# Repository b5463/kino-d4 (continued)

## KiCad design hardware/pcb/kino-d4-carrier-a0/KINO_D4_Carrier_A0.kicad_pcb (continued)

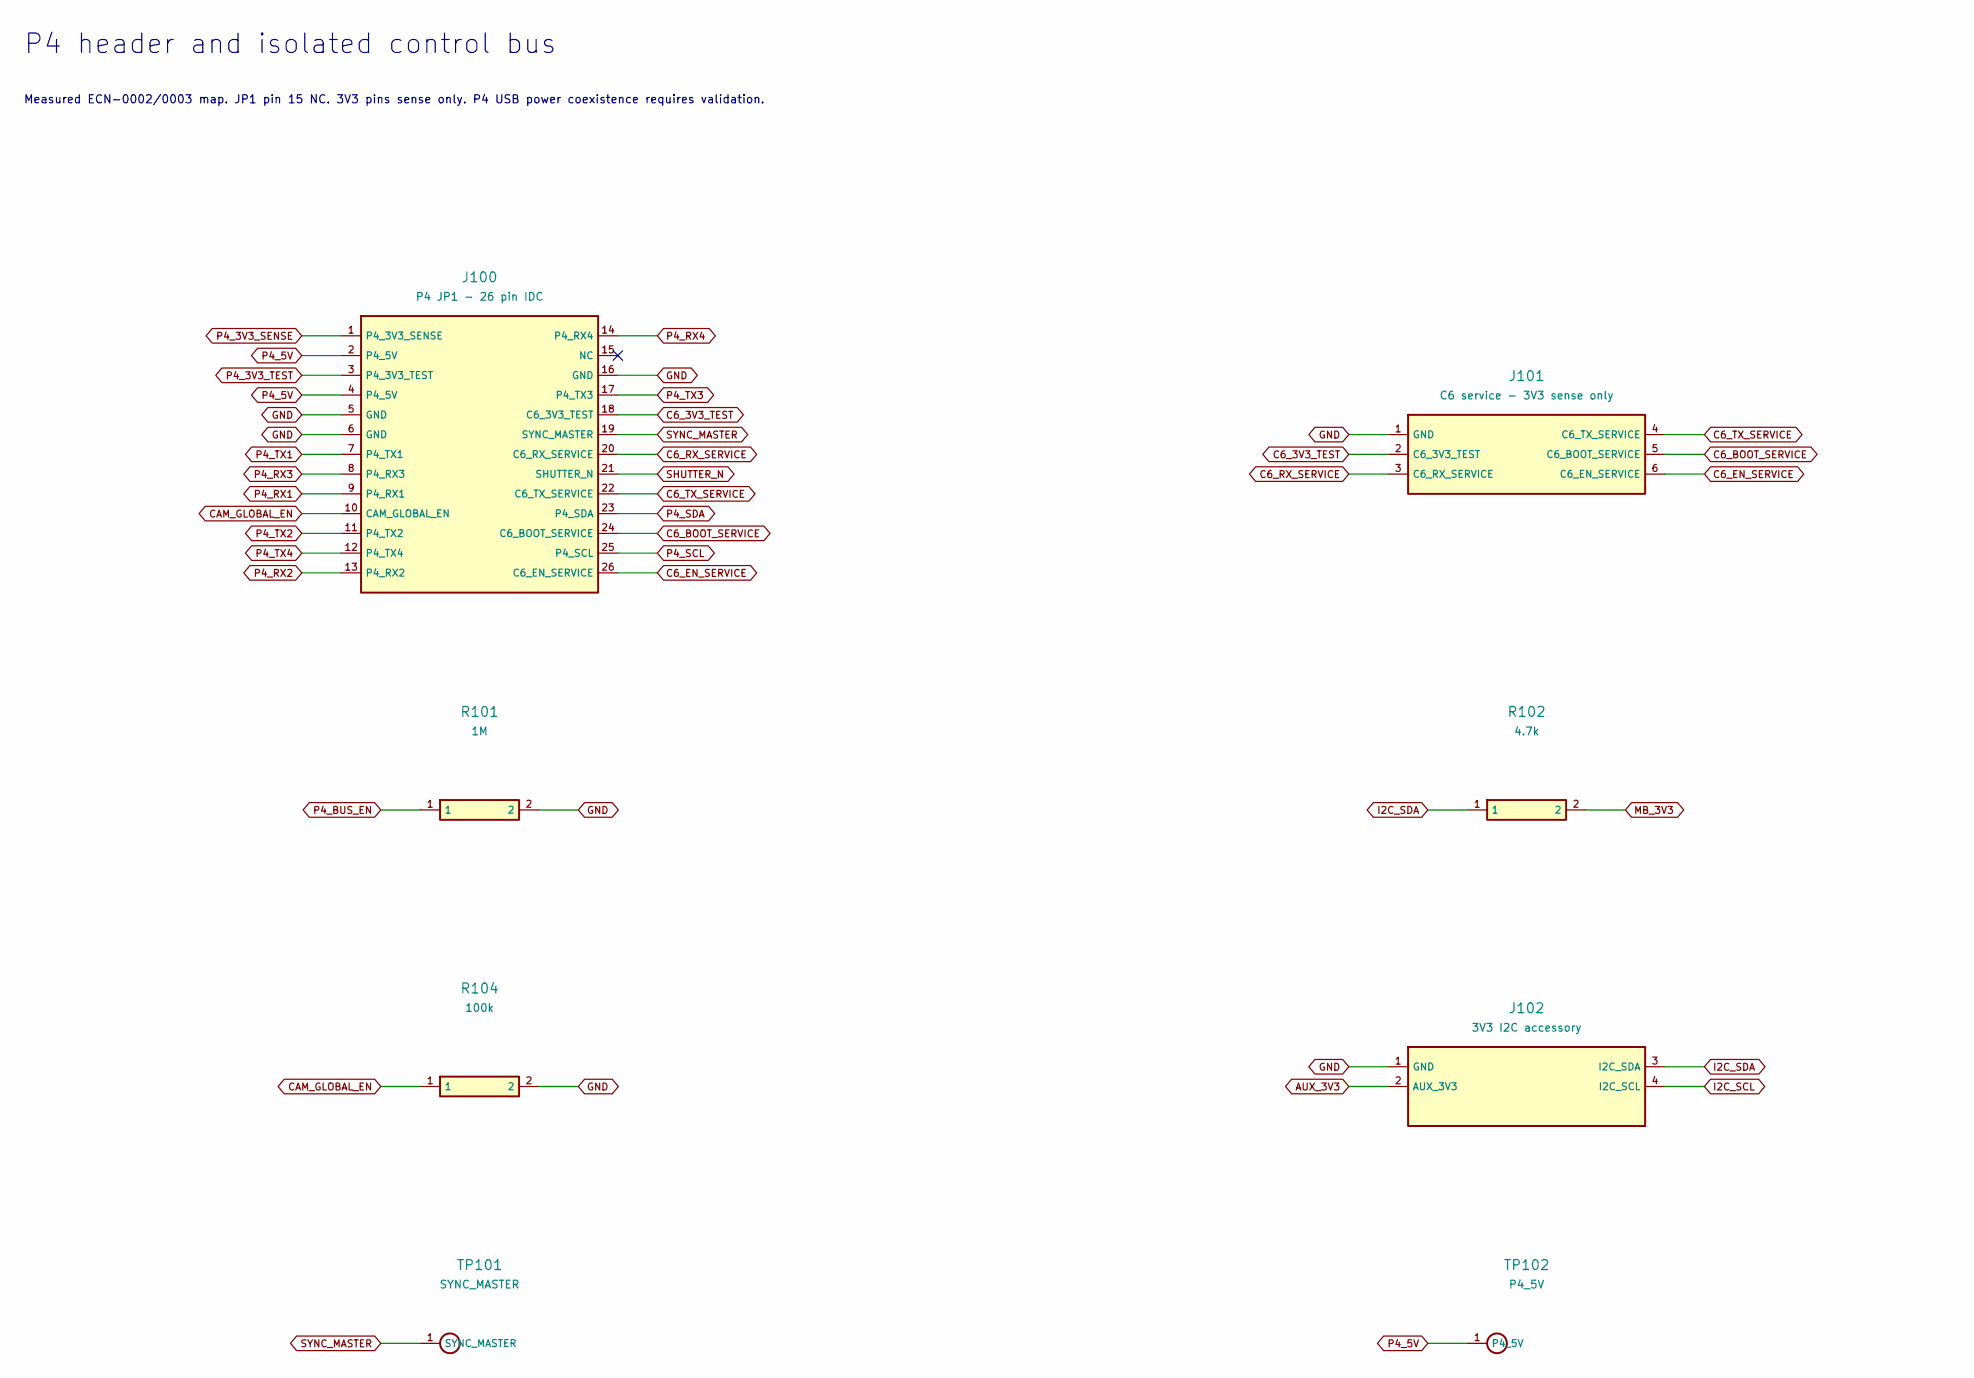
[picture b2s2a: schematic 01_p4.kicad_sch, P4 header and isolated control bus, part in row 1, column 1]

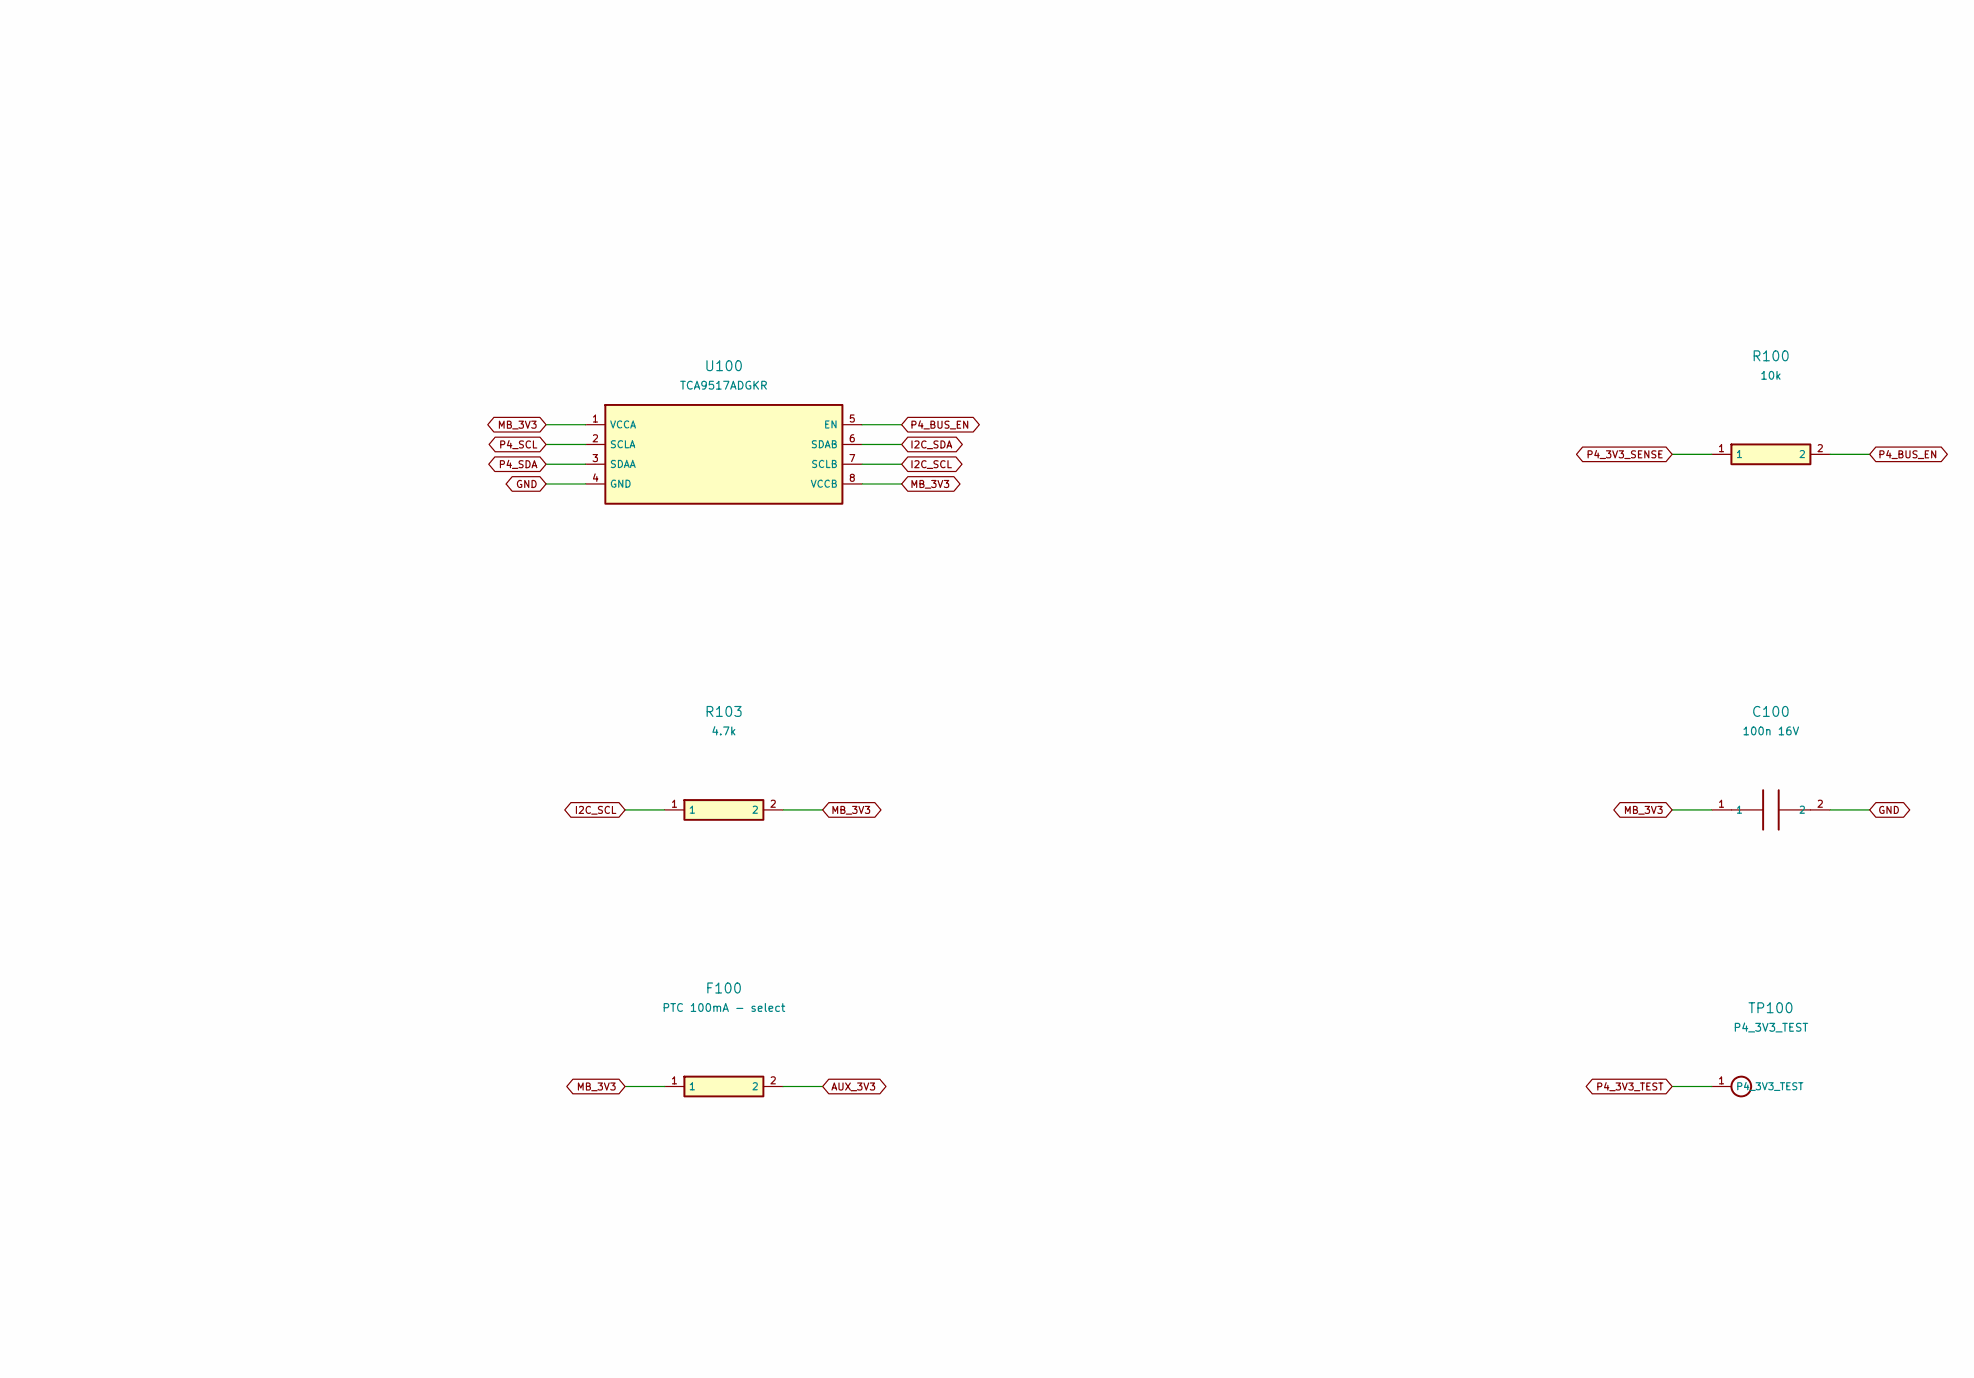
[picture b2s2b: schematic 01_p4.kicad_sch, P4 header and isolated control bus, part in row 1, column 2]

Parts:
C100: 100n 16V; C_0603_1608Metric
F100: PTC 100mA - select; Fuse_1206_3216Metric
J100: P4 JP1 - 26 pin IDC; IDC-Header_2x13_P2.54mm_Vertical
J101: C6 service - 3V3 sense only; PinHeader_1x06_P2.54mm_Vertical
J102: 3V3 I2C accessory; JST_GH_BM04B-GHS-TBT_1x04-1MP_P1.25mm_Vertical
R100: 10k; R_0603_1608Metric
R101: 1M; R_0603_1608Metric
R102, R103: 4.7k; R_0603_1608Metric
R104: 100k; R_0603_1608Metric
TP100: P4_3V3_TEST; TestPoint_Pad_D1.5mm
TP101: SYNC_MASTER; TestPoint_Pad_D1.5mm
TP102: P4_5V; TestPoint_Pad_D1.5mm
U100: TCA9517ADGKR; VSSOP-8_3x3mm_P0.65mm

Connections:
AUX_3V3: F100.2, J102.2 (AUX_3V3)
C6_3V3_TEST: J100.18 (C6_3V3_TEST), J101.2 (C6_3V3_TEST)
C6_BOOT_SERVICE: J100.24 (C6_BOOT_SERVICE), J101.5 (C6_BOOT_SERVICE)
C6_EN_SERVICE: J100.26 (C6_EN_SERVICE), J101.6 (C6_EN_SERVICE)
C6_RX_SERVICE: J100.20 (C6_RX_SERVICE), J101.3 (C6_RX_SERVICE)
C6_TX_SERVICE: J100.22 (C6_TX_SERVICE), J101.4 (C6_TX_SERVICE)
CAM_GLOBAL_EN: J100.10 (CAM_GLOBAL_EN), R104.1; also elsewhere on the board
I2C_SCL: J102.4 (I2C_SCL), R103.1, U100.7 (SCLB); also elsewhere on the board
I2C_SDA: J102.3 (I2C_SDA), R102.1, U100.6 (SDAB); also elsewhere on the board
MB_3V3: C100.1, F100.1, R102.2, R103.2, U100.1 (VCCA), U100.8 (VCCB); also elsewhere on the board
P4_3V3_SENSE: J100.1 (P4_3V3_SENSE), R100.1
P4_3V3_TEST: J100.3 (P4_3V3_TEST), TP100.1
P4_5V: J100.2 (P4_5V), J100.4 (P4_5V), TP102.1; also elsewhere on the board
P4_BUS_EN: R100.2, R101.1, U100.5 (EN); also elsewhere on the board
P4_RX1: J100.9 (P4_RX1); also elsewhere on the board
P4_RX2: J100.13 (P4_RX2); also elsewhere on the board
P4_RX3: J100.8 (P4_RX3); also elsewhere on the board
P4_RX4: J100.14 (P4_RX4); also elsewhere on the board
P4_SCL: J100.25 (P4_SCL), U100.2 (SCLA)
P4_SDA: J100.23 (P4_SDA), U100.3 (SDAA)
P4_TX1: J100.7 (P4_TX1); also elsewhere on the board
P4_TX2: J100.11 (P4_TX2); also elsewhere on the board
P4_TX3: J100.17 (P4_TX3); also elsewhere on the board
P4_TX4: J100.12 (P4_TX4); also elsewhere on the board
SHUTTER_N: J100.21 (SHUTTER_N); also elsewhere on the board
SYNC_MASTER: J100.19 (SYNC_MASTER), TP101.1; also elsewhere on the board

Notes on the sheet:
P4 header and isolated control bus
Measured ECN-0002/0003 map. JP1 pin 15 NC. 3V3 pins sense only. P4 USB power coexistence requires validation.

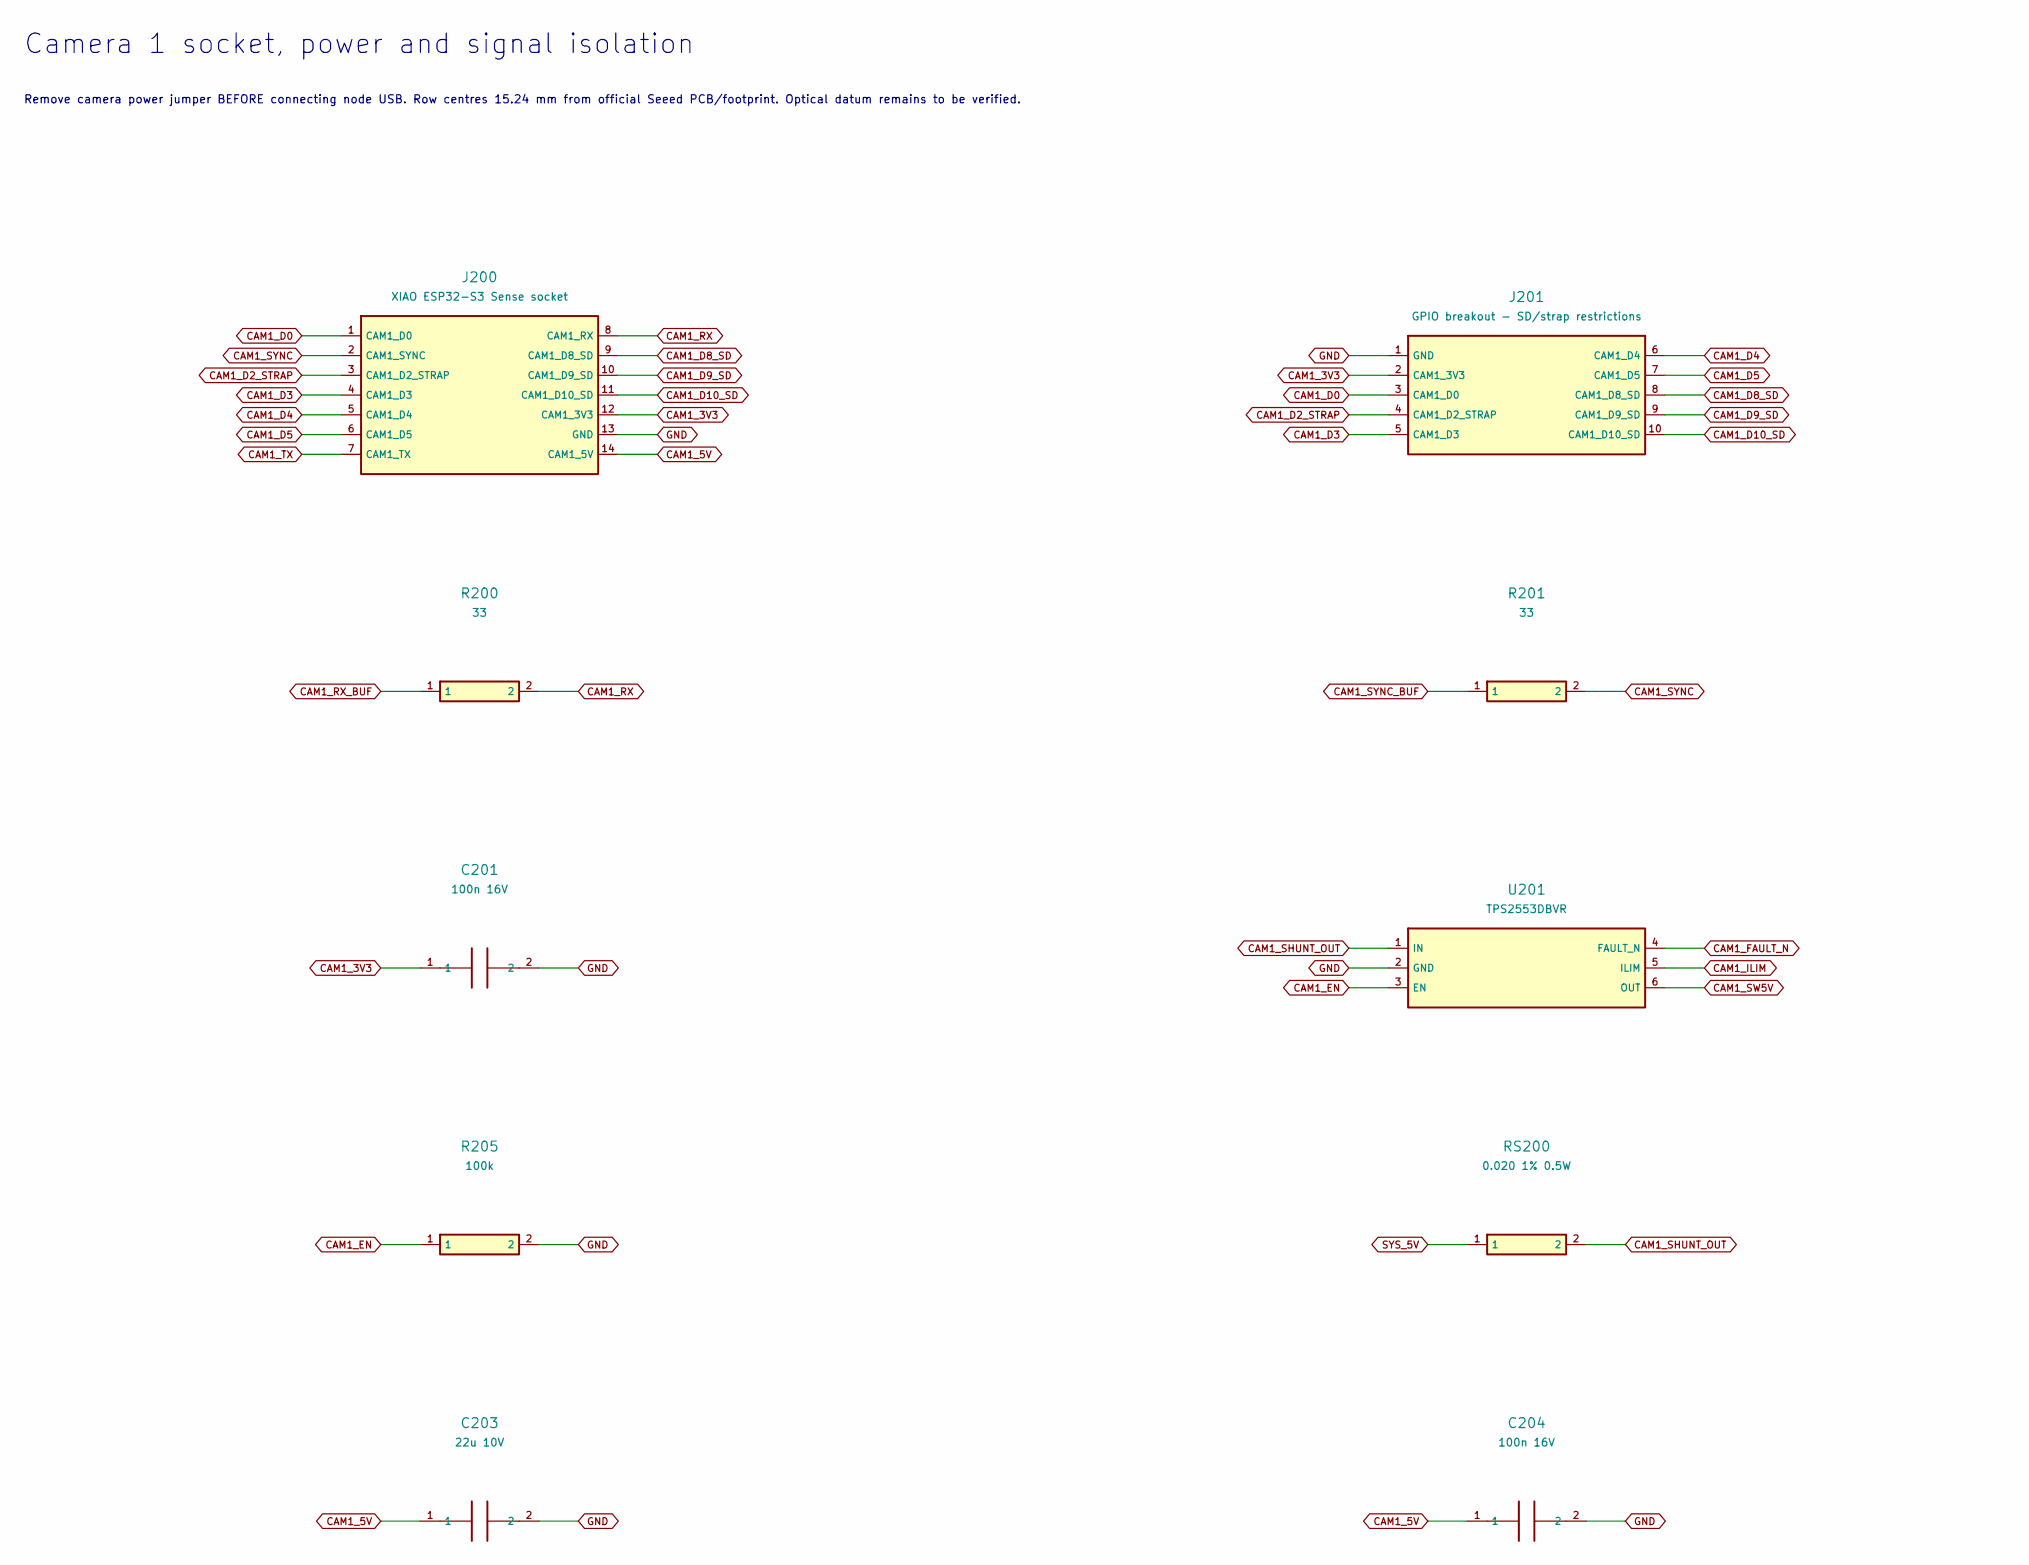
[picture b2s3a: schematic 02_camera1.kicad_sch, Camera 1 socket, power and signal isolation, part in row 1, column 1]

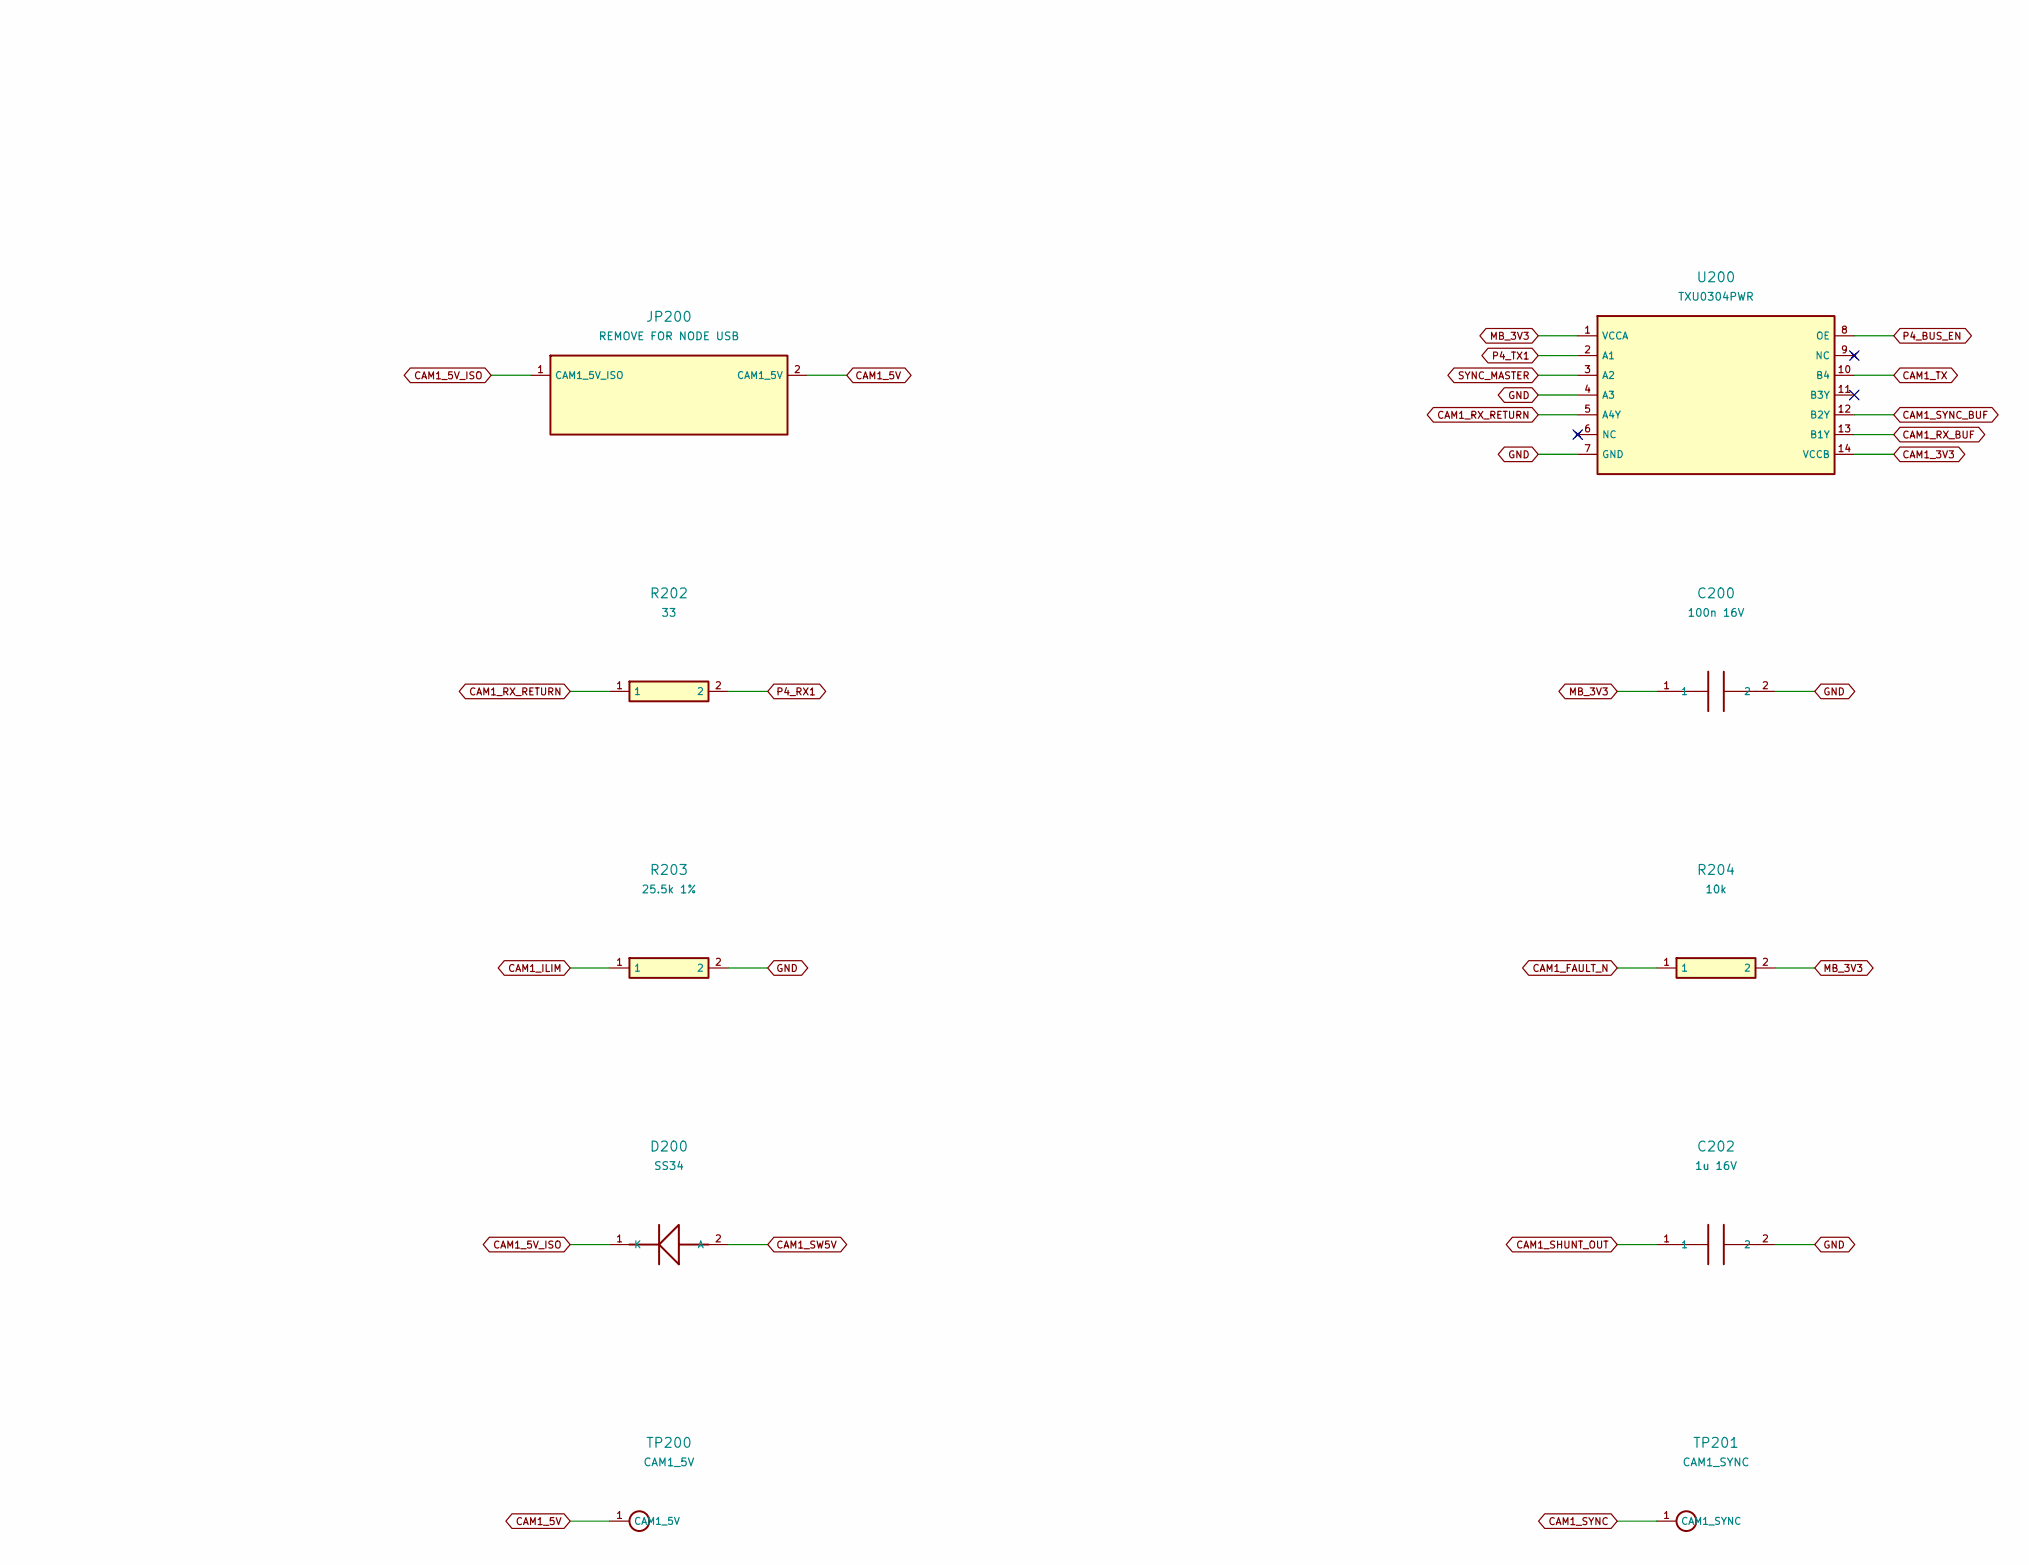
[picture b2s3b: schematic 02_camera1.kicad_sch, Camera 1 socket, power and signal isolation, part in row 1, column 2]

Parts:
C200, C201, C204: 100n 16V; C_0603_1608Metric
C202: 1u 16V; C_0603_1608Metric
C203: 22u 10V; C_0805_2012Metric
D200: SS34; D_SMA
J200: XIAO ESP32-S3 Sense socket; XIAO_Socket_15.24mm
J201: GPIO breakout - SD/strap restrictions; PinHeader_2x05_P2.54mm_Vertical
JP200: REMOVE FOR NODE USB; PinHeader_1x02_P2.54mm_Vertical
R200, R201, R202: 33; R_0603_1608Metric
R203: 25.5k 1%; R_0603_1608Metric
R204: 10k; R_0603_1608Metric
R205: 100k; R_0603_1608Metric
RS200: 0.020 1% 0.5W; R_1206_3216Metric
TP200: CAM1_5V; TestPoint_Pad_D1.5mm
TP201: CAM1_SYNC; TestPoint_Pad_D1.5mm
U200: TXU0304PWR; TSSOP-14_4.4x5mm_P0.65mm
U201: TPS2553DBVR; SOT-23-6

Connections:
CAM1_3V3: C201.1, J200.12 (CAM1_3V3), J201.2 (CAM1_3V3), U200.14 (VCCB)
CAM1_5V: C203.1, C204.1, J200.14 (CAM1_5V), JP200.2 (CAM1_5V), TP200.1
CAM1_5V_ISO: D200.1 (K), JP200.1 (CAM1_5V_ISO)
CAM1_D0: J200.1 (CAM1_D0), J201.3 (CAM1_D0)
CAM1_D2_STRAP: J200.3 (CAM1_D2_STRAP), J201.4 (CAM1_D2_STRAP)
CAM1_D3: J200.4 (CAM1_D3), J201.5 (CAM1_D3)
CAM1_D4: J200.5 (CAM1_D4), J201.6 (CAM1_D4)
CAM1_D5: J200.6 (CAM1_D5), J201.7 (CAM1_D5)
CAM1_D8_SD: J200.9 (CAM1_D8_SD), J201.8 (CAM1_D8_SD)
CAM1_D9_SD: J200.10 (CAM1_D9_SD), J201.9 (CAM1_D9_SD)
CAM1_D10_SD: J200.11 (CAM1_D10_SD), J201.10 (CAM1_D10_SD)
CAM1_EN: R205.1, U201.3 (EN); also elsewhere on the board
CAM1_FAULT_N: R204.1, U201.4 (FAULT_N); also elsewhere on the board
CAM1_ILIM: R203.1, U201.5 (ILIM)
CAM1_RX: J200.8 (CAM1_RX), R200.2
CAM1_RX_BUF: R200.1, U200.13 (B1Y)
CAM1_RX_RETURN: R202.1, U200.5 (A4Y)
CAM1_SHUNT_OUT: C202.1, RS200.2, U201.1 (IN); also elsewhere on the board
CAM1_SW5V: D200.2 (A), U201.6 (OUT)
CAM1_SYNC: J200.2 (CAM1_SYNC), R201.2, TP201.1
CAM1_SYNC_BUF: R201.1, U200.12 (B2Y)
CAM1_TX: J200.7 (CAM1_TX), U200.10 (B4)
MB_3V3: C200.1, R204.2, U200.1 (VCCA); also elsewhere on the board
P4_BUS_EN: U200.8 (OE); also elsewhere on the board
P4_RX1: R202.2; also elsewhere on the board
P4_TX1: U200.2 (A1); also elsewhere on the board
SYNC_MASTER: U200.3 (A2); also elsewhere on the board
SYS_5V: RS200.1; also elsewhere on the board

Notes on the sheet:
Camera 1 socket, power and signal isolation
Remove camera power jumper BEFORE connecting node USB. Row centres 15.24 mm from official Seeed PCB/footprint. Optical datum remains to be verified.

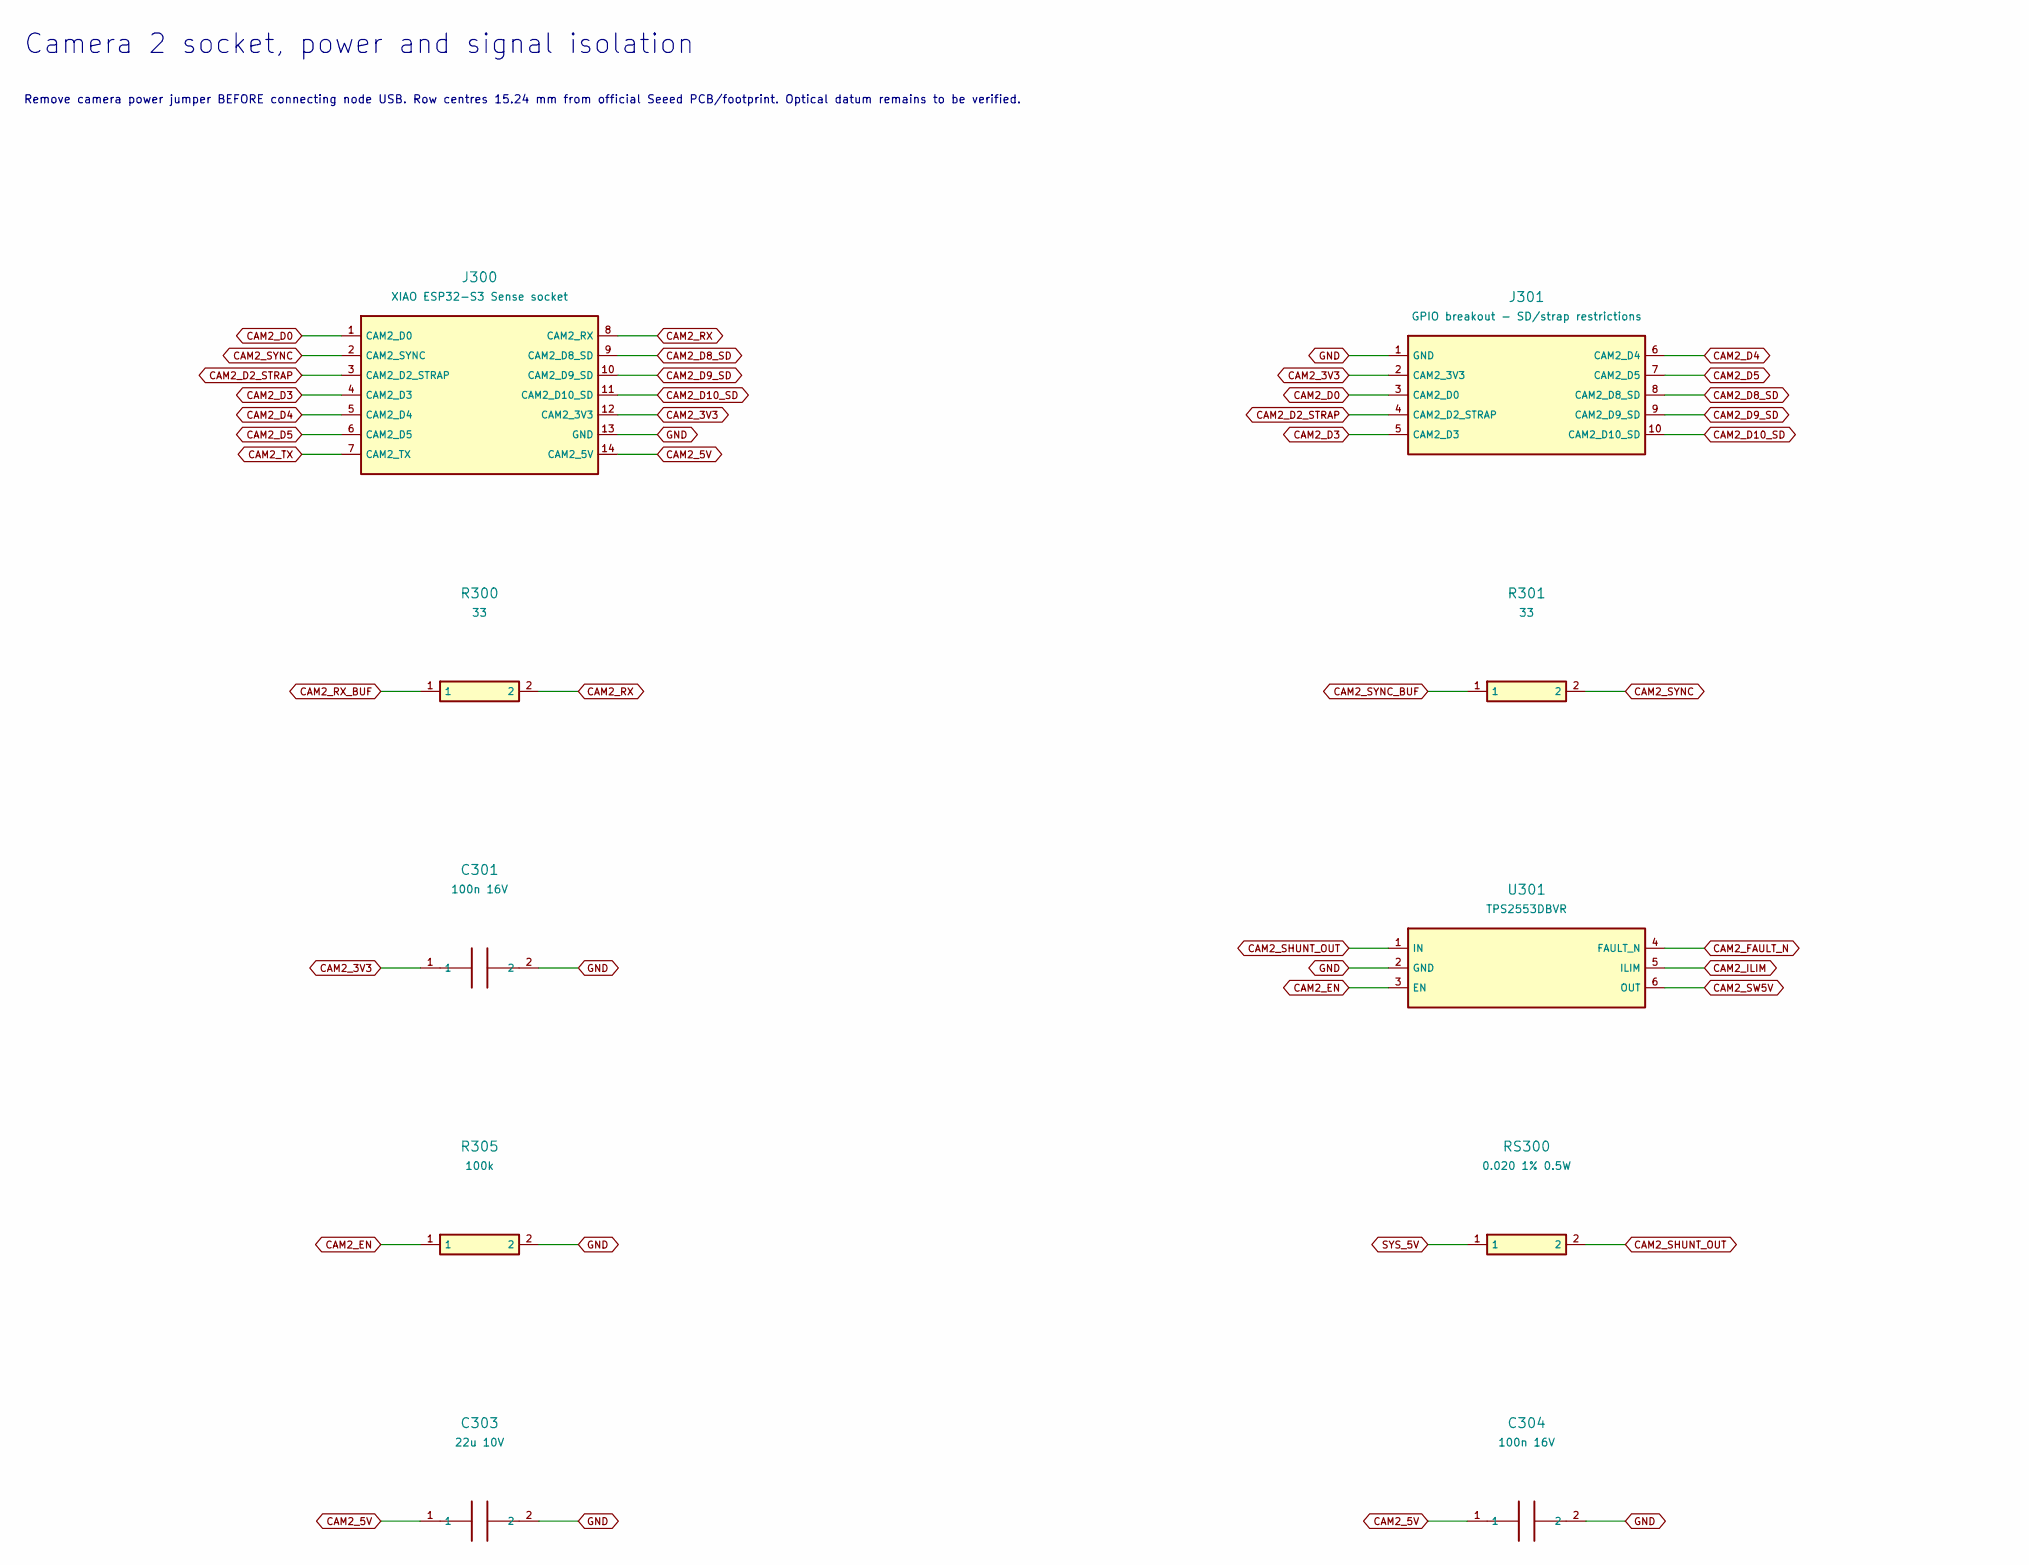
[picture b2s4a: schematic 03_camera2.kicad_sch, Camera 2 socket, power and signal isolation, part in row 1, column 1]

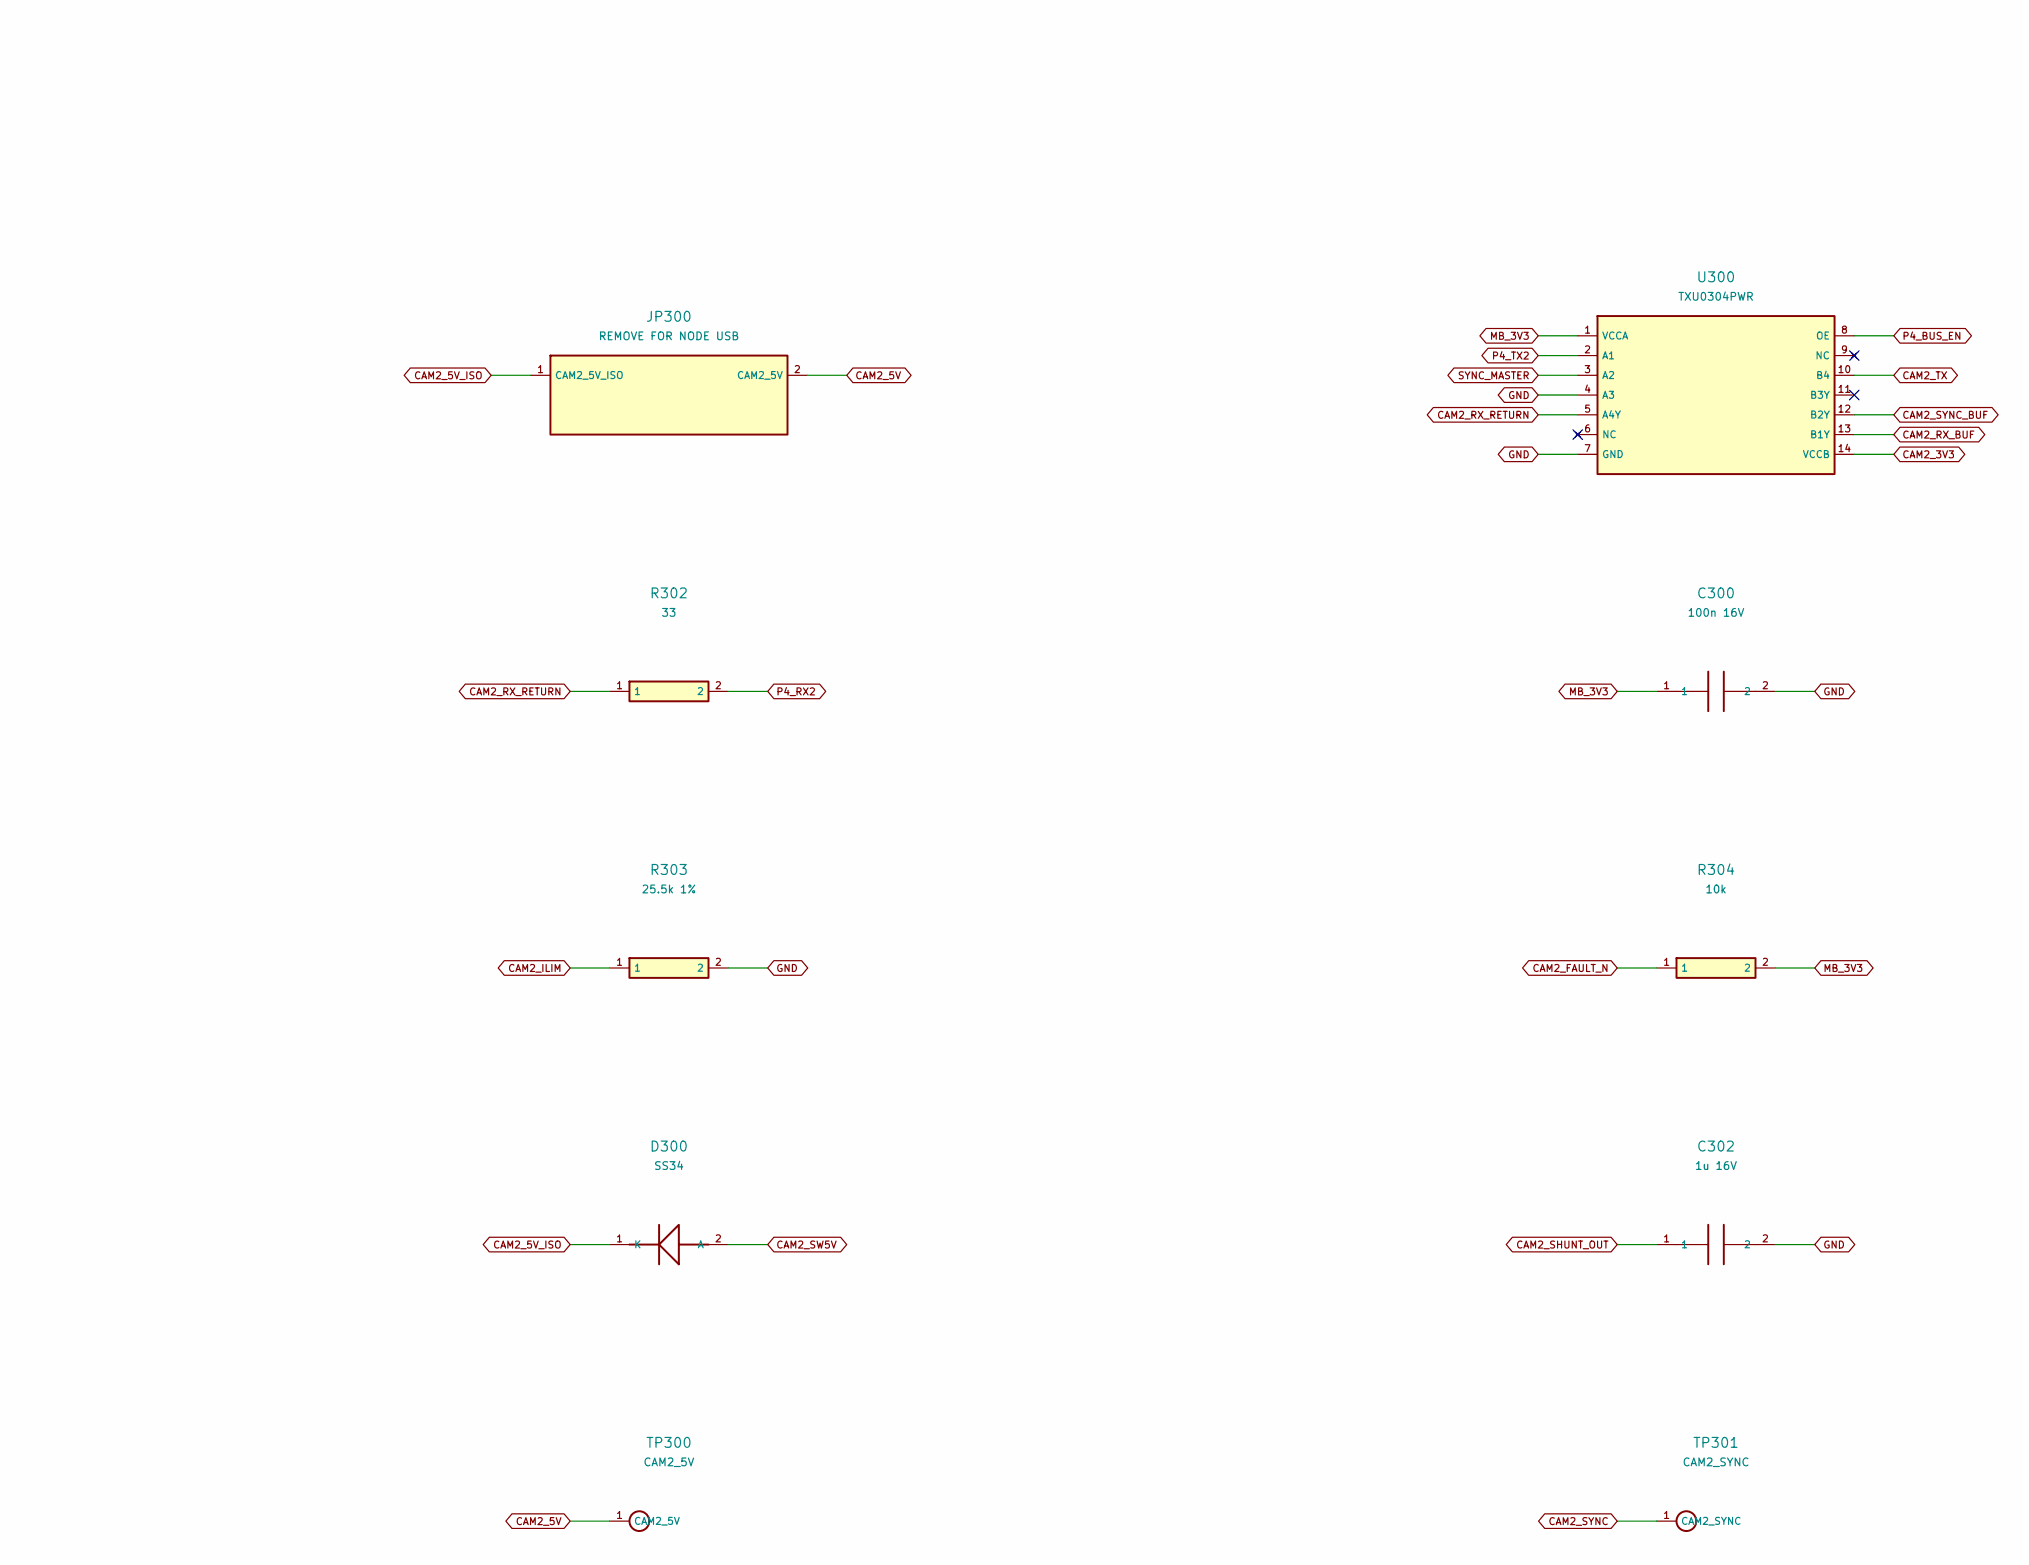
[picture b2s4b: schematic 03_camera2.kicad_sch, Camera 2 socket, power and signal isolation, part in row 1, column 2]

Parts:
C300, C301, C304: 100n 16V; C_0603_1608Metric
C302: 1u 16V; C_0603_1608Metric
C303: 22u 10V; C_0805_2012Metric
D300: SS34; D_SMA
J300: XIAO ESP32-S3 Sense socket; XIAO_Socket_15.24mm
J301: GPIO breakout - SD/strap restrictions; PinHeader_2x05_P2.54mm_Vertical
JP300: REMOVE FOR NODE USB; PinHeader_1x02_P2.54mm_Vertical
R300, R301, R302: 33; R_0603_1608Metric
R303: 25.5k 1%; R_0603_1608Metric
R304: 10k; R_0603_1608Metric
R305: 100k; R_0603_1608Metric
RS300: 0.020 1% 0.5W; R_1206_3216Metric
TP300: CAM2_5V; TestPoint_Pad_D1.5mm
TP301: CAM2_SYNC; TestPoint_Pad_D1.5mm
U300: TXU0304PWR; TSSOP-14_4.4x5mm_P0.65mm
U301: TPS2553DBVR; SOT-23-6

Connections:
CAM2_3V3: C301.1, J300.12 (CAM2_3V3), J301.2 (CAM2_3V3), U300.14 (VCCB)
CAM2_5V: C303.1, C304.1, J300.14 (CAM2_5V), JP300.2 (CAM2_5V), TP300.1
CAM2_5V_ISO: D300.1 (K), JP300.1 (CAM2_5V_ISO)
CAM2_D0: J300.1 (CAM2_D0), J301.3 (CAM2_D0)
CAM2_D2_STRAP: J300.3 (CAM2_D2_STRAP), J301.4 (CAM2_D2_STRAP)
CAM2_D3: J300.4 (CAM2_D3), J301.5 (CAM2_D3)
CAM2_D4: J300.5 (CAM2_D4), J301.6 (CAM2_D4)
CAM2_D5: J300.6 (CAM2_D5), J301.7 (CAM2_D5)
CAM2_D8_SD: J300.9 (CAM2_D8_SD), J301.8 (CAM2_D8_SD)
CAM2_D9_SD: J300.10 (CAM2_D9_SD), J301.9 (CAM2_D9_SD)
CAM2_D10_SD: J300.11 (CAM2_D10_SD), J301.10 (CAM2_D10_SD)
CAM2_EN: R305.1, U301.3 (EN); also elsewhere on the board
CAM2_FAULT_N: R304.1, U301.4 (FAULT_N); also elsewhere on the board
CAM2_ILIM: R303.1, U301.5 (ILIM)
CAM2_RX: J300.8 (CAM2_RX), R300.2
CAM2_RX_BUF: R300.1, U300.13 (B1Y)
CAM2_RX_RETURN: R302.1, U300.5 (A4Y)
CAM2_SHUNT_OUT: C302.1, RS300.2, U301.1 (IN); also elsewhere on the board
CAM2_SW5V: D300.2 (A), U301.6 (OUT)
CAM2_SYNC: J300.2 (CAM2_SYNC), R301.2, TP301.1
CAM2_SYNC_BUF: R301.1, U300.12 (B2Y)
CAM2_TX: J300.7 (CAM2_TX), U300.10 (B4)
MB_3V3: C300.1, R304.2, U300.1 (VCCA); also elsewhere on the board
P4_BUS_EN: U300.8 (OE); also elsewhere on the board
P4_RX2: R302.2; also elsewhere on the board
P4_TX2: U300.2 (A1); also elsewhere on the board
SYNC_MASTER: U300.3 (A2); also elsewhere on the board
SYS_5V: RS300.1; also elsewhere on the board

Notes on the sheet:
Camera 2 socket, power and signal isolation
Remove camera power jumper BEFORE connecting node USB. Row centres 15.24 mm from official Seeed PCB/footprint. Optical datum remains to be verified.
